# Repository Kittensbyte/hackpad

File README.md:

# kittenbyte-hackpad
https://blueprint.hackclub.com/hackpad

This is a my first project for hackclub and it is a 6-key macropad.

## Features:
Customizable keypad with six mechanical buttons designed to automate complex commands.

Custom pcb that is small and powered by usb.

3D printed case

MX-Style switches 6 Keys (2 X 3)

2 WS2812B RGB LEDs

## CAD Model:
The case fits together using 5 M3 Bolts
There are 2 parts the bottom of the case and the top lid of the case.

(I made this with Fusion360)

## PCB
Below is my PCB made with KiCad. 
The logo was created by me with photoshop and imported.

## Firmware Overview
This hackpad uses the [QMK firmware project](https://qmk.fm/) as firmware!

## BOM:
This is what you need to make this hackpad.

- 1x XIAO RP2040
- 1x Case (2 printed parts)
- 6x Cherry MX Switches
- 6x DSA Keycaps
- 3x M3x16mm SHCS Bolts
- 2X M3x12mm SHCS Bolts
- 2x WS2812B LEDs

## Extra info
This was my first project and I have valued this so much.

Special thanks to [hackclub](https://https://hackclub.com/)

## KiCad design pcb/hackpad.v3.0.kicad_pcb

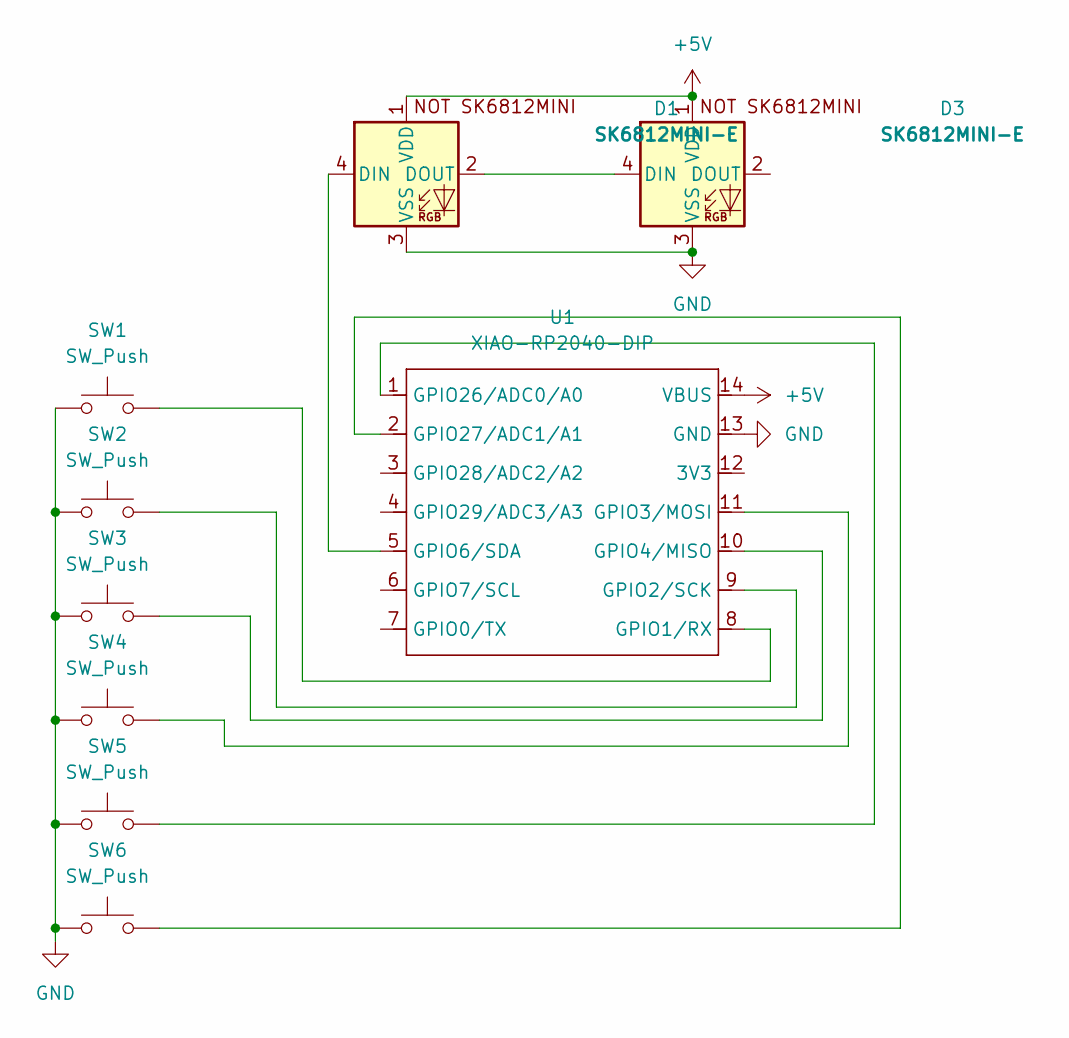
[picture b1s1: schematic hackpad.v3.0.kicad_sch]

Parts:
D1, D3: SK6812MINI-E; SK6812MINI-E_fixed
SW1, SW2, SW3, SW4, SW5, SW6: SW_Push; SW_Cherry_MX_1.00u_PCB
U1: XIAO-RP2040-DIP

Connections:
+5V: D1.1 (VDD), D3.1 (VDD), U1.14 (VBUS)
GND: D1.3 (VSS), D3.3 (VSS), SW1.1, SW2.1, SW3.1, SW4.1, SW5.1, SW6.1, U1.13 (GND)
unnamed: D1.4 (DIN), U1.5 (GPIO6/SDA)
unnamed: D1.2 (DOUT), D3.4 (DIN)
unnamed: SW1.2, U1.8 (GPIO1/RX)
unnamed: SW2.2, U1.9 (GPIO2/SCK)
unnamed: SW4.2, U1.11 (GPIO3/MOSI)
unnamed: SW3.2, U1.10 (GPIO4/MISO)
unnamed: SW5.2, U1.1 (GPIO26/ADC0/A0)
unnamed: SW6.2, U1.2 (GPIO27/ADC1/A1)

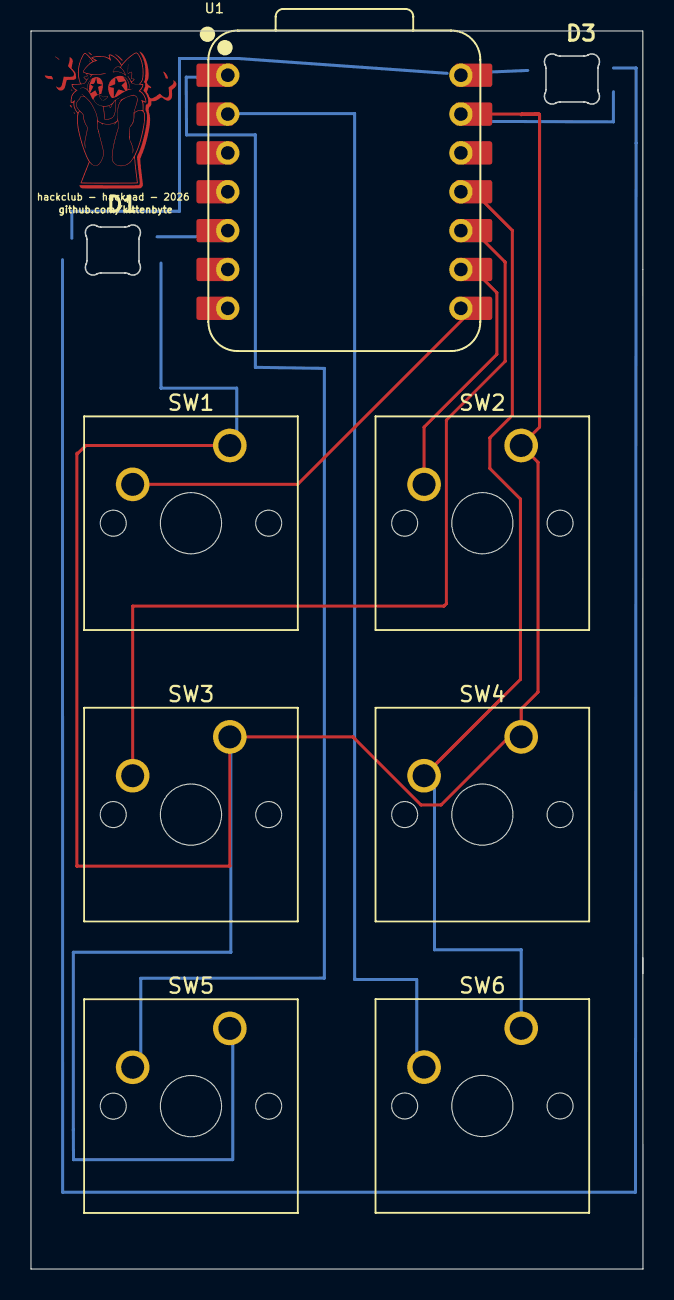
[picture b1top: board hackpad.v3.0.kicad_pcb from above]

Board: 2 copper layers, 40.0 x 80.9 mm, 11 parts (0 on the bottom side), 10 nets.

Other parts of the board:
 : LOGO; logo - Copy
 #2: LOGO; logo
